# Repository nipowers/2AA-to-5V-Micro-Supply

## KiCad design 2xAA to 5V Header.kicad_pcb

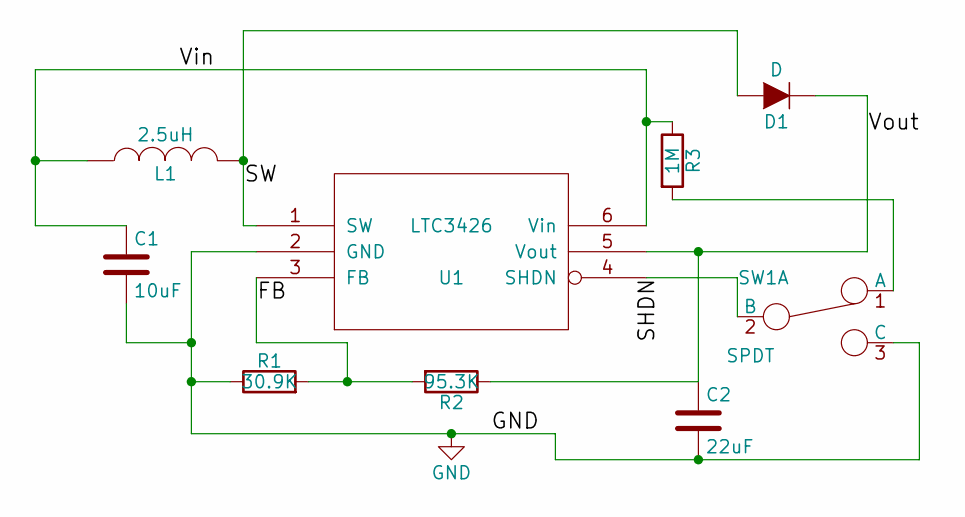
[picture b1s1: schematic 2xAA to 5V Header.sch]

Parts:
C1: 10uF; C_0805_HandSoldering; Part Number CL21A106KQFNNNG
C2: 22uF; C_0805_HandSoldering; Part Number CL21A226MQQNNNG
D1: D; POWERMITE; Part Number MBRM120LT3G
L1: 2.5uH; C_0805_HandSoldering; Part Number MLZ2012M2R2HT
R1: 30.9K; R_0805_HandSoldering; Part Number ERJ-6ENF30R9V
R2: 95.3K; R_0805_HandSoldering; Part Number ERJ-6ENF95R3V
R3: 1M; R_0805_HandSoldering; Part Number RC2012J105CS
SW1: SPDT; JS102011SAQN; Part Number JS102011SAQN
U1: LTC3426; SOT-23-6; Part Number LTC3426ES6

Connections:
/FB: R1.2, R2.2, U1.3 (FB)
/SHDN: SW1.2 (B), U1.4 (SHDN)
/SW: D1.2 (A), L1.2, U1.1 (SW)
/Vin: C1.1, L1.1, R3.1, U1.6 (Vin)
/Vout: C2.1, D1.1 (K), R2.1, U1.5 (Vout); also elsewhere on the board
GND: C1.2, C2.2, R1.1, SW1.3 (C), U1.2 (GND); also elsewhere on the board
unnamed: R3.2, SW1.1 (A)

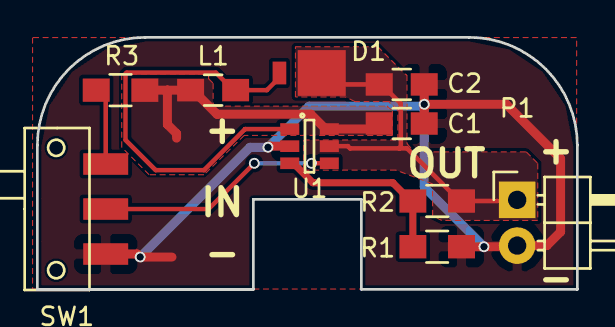
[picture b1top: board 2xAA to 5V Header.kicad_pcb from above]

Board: 2 copper layers, 30.0 x 14.0 mm, 10 parts (0 on the bottom side), 7 nets.

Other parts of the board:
P1: CONN_01X02; Pin_Header_Angled_1x02

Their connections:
/Vout: P1.1; also elsewhere on the board
GND: P1.2; also elsewhere on the board

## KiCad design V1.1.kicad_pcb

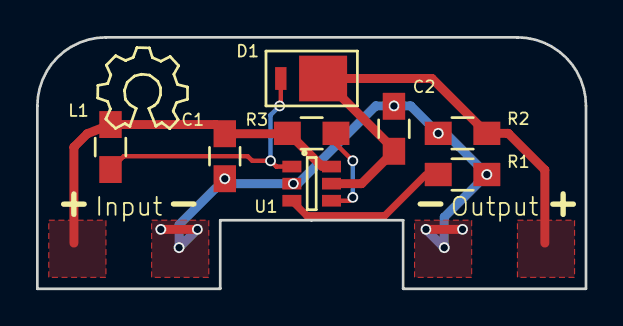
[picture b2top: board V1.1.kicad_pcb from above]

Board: 2 copper layers, 30.5 x 14.0 mm, 8 parts (0 on the bottom side), 6 nets.

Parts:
C1: 10uF; C_0805_HandSoldering
C2: 22uF; C_0805_HandSoldering
D1: POWERMITE2
L1: 2.5uH; C_0805_HandSoldering
R1: 95.3k; R_0805_HandSoldering
R2: 30.9K; R_0805_HandSoldering
R3: 1M; R_0805_HandSoldering
U1: LTC3426; SOT-23-6

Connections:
/FB: R1.1, U1.3
/SHDN: R3.2, U1.4
/SW: D1.2, L1.2, U1.1
/Vin: C1.1, L1.1, R3.1, U1.6
/Vout: C2.1, D1.1, R2.1, U1.5
GND: C1.2, C2.2, R1.2, R2.2, U1.2

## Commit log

2016-03-14 :boom::camel: Added .gitattributes & .gitignore files
2016-03-14 Initial
    Initial commit of in progress project
2016-03-29 PDF output of layers
    Created PDF outputs of the board layers to more easily print and share.
2016-03-29 Pin header and corners
    Added a two pin header for the output to make attaching leads easier and
    cleaned up any 90 degree corners in fills.
2016-03-29 Redo of GND copper fill
    Reworked the GND copper fills to cover better and use thermal reliefs.
2016-03-29 Adjust Bottom Copper Fill
2016-03-30 Minor revisions
